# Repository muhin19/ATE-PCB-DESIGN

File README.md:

ATE PCB Design

📌 Project Overview
This project involves the design and development of a Printed Circuit Board (PCB) for an Automatic Test Equipment (ATE) application. It includes PCB layout design, component placement, track routing, and design verification to achieve a reliable and organized hardware layout.

🎯 Objectives
Design a PCB layout for an ATE application.
Arrange electronic components efficiently.
Route signal and power connections properly.
Maintain a clear and organized PCB layout.
Prepare PCB design files for manufacturing and further testing.

🛠️ Tools Used
PCB Design Software: KiCad
Schematic Design
Component Placement and Routing
Design Rule Check (DRC)

📂 Project Files
Schematic/ – Circuit schematic files.
PCB_Layout/ – PCB layout and board design files.
Gerber/ – Manufacturing output files, if available.
BOM/ – Bill of Materials, if available.
Images/ – PCB layout screenshots and 3D views.

⚙️ Design Features
Organized component placement.
PCB trace routing and connectivity.
Power and signal routing considerations.
Design verification using applicable PCB design rules.
Manufacturing file generation, if completed.

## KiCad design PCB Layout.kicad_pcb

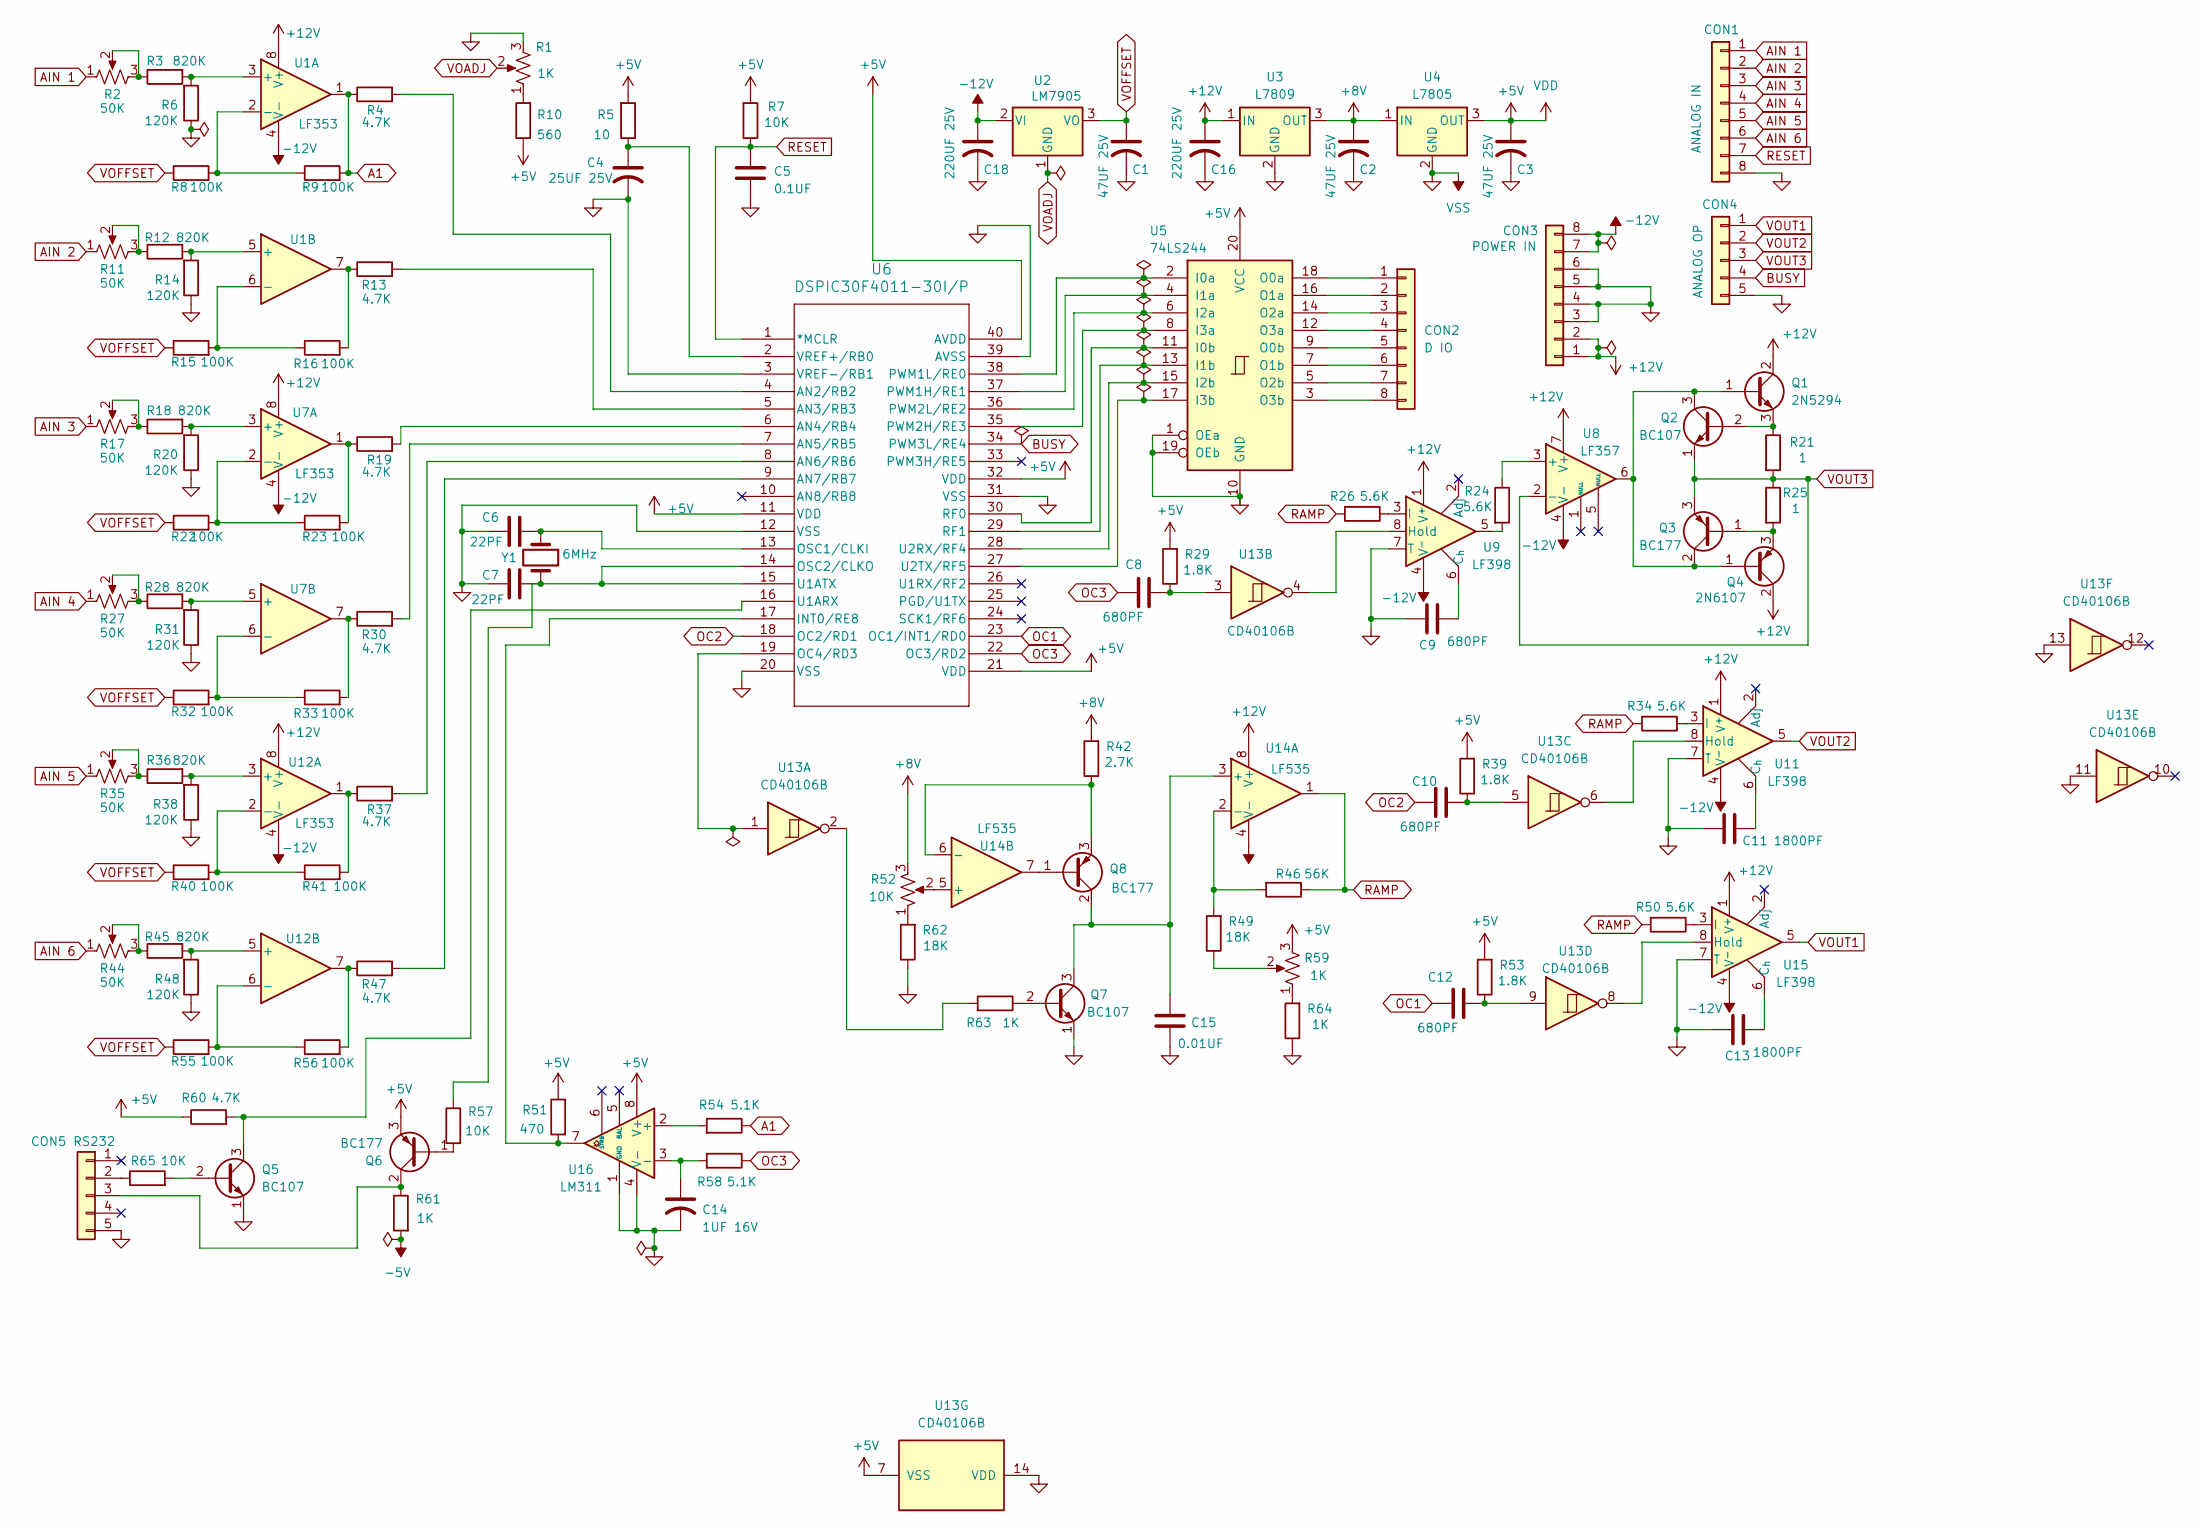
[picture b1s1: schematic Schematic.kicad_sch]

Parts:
C1, C2, C3: 47UF 25V; C_Radial_D5.0mm_H11.0mm_P2.00mm
C4: 25UF 25V; C_Radial_D5.0mm_H11.0mm_P2.00mm
C5: 0.1UF; C_Radial_D5.0mm_H11.0mm_P2.00mm
C6, C7: 22PF; C_Disc_D5.1mm_W3.2mm_P5.00mm
C8, C9, C10, C12: 680PF; C_Disc_D6.0mm_W4.4mm_P5.00mm
C11, C13: 1800PF; C_Disc_D6.0mm_W4.4mm_P5.00mm
C14: 1UF 16V; C_Radial_D5.0mm_H11.0mm_P2.00mm
C15: 0.01UF; C_Axial_L17.0mm_D6.5mm_P20.00mm_Horizontal
C16, C18: 220UF 25V; C_Radial_D8.0mm_H11.5mm_P3.50mm
CON1: ANALOG IN; JST_XH_B8B-XH-A_1x08_P2.50mm_Vertical
CON2: D IO; JST_XH_B8B-XH-A_1x08_P2.50mm_Vertical
CON3: POWER IN; JST_XH_B8B-XH-A_1x08_P2.50mm_Vertical
CON4: ANALOG OP; JST_XH_B5B-XH-A_1x05_P2.50mm_Vertical
CON5: RS232; JST_XH_B5B-XH-A_1x05_P2.50mm_Vertical
Q1: 2N5294; TO-220-3_Vertical
Q2, Q5, Q7: BC107; TO-18-3
Q3, Q6, Q8: BC177; TO-18-3
Q4: 2N6107; TO-220-3_Vertical
R1, R59: 1K; Potentiometer_Bourns_3296W_Vertical
R2, R11, R17, R27, R35, R44: 50K; Potentiometer_Bourns_3296W_Vertical
R3, R12, R18, R28, R36, R45: 820K; R_Axial_DIN0207_L6.3mm_D2.5mm_P10.16mm_Horizontal
R4, R13, R19, R30, R37, R47, R60: 4.7K; R_Axial_DIN0207_L6.3mm_D2.5mm_P10.16mm_Horizontal
R5: 10; R_Axial_DIN0207_L6.3mm_D2.5mm_P10.16mm_Horizontal
R6, R14, R20, R31, R38, R48: 120K; R_Axial_DIN0207_L6.3mm_D2.5mm_P10.16mm_Horizontal
R7, R57, R65: 10K; R_Axial_DIN0207_L6.3mm_D2.5mm_P10.16mm_Horizontal
R8, R9, R15, R16, R22, R23, R32, R33, R40, R41, R55, R56: 100K; R_Axial_DIN0207_L6.3mm_D2.5mm_P10.16mm_Horizontal
R10: 560; R_Axial_DIN0207_L6.3mm_D2.5mm_P10.16mm_Horizontal
R21, R25: 1; R_Axial_DIN0207_L6.3mm_D2.5mm_P10.16mm_Horizontal
R24, R26, R34, R50: 5.6K; R_Axial_DIN0207_L6.3mm_D2.5mm_P10.16mm_Horizontal
R29, R39, R53: 1.8K; R_Axial_DIN0207_L6.3mm_D2.5mm_P10.16mm_Horizontal
R42: 2.7K; R_Axial_DIN0207_L6.3mm_D2.5mm_P10.16mm_Horizontal
R46: 56K; R_Axial_DIN0207_L6.3mm_D2.5mm_P10.16mm_Horizontal
R49, R62: 18K; R_Axial_DIN0207_L6.3mm_D2.5mm_P10.16mm_Horizontal
R51: 470; R_Axial_DIN0207_L6.3mm_D2.5mm_P10.16mm_Horizontal
R52: 10K; Potentiometer_Bourns_3296W_Vertical
R54, R58: 5.1K; R_Axial_DIN0207_L6.3mm_D2.5mm_P10.16mm_Horizontal
R61, R63, R64: 1K; R_Axial_DIN0207_L6.3mm_D2.5mm_P10.16mm_Horizontal
U1, U7, U12: LF353; DIP-8_W7.62mm
U2: LM7905; TO-220-3_Vertical
U3: L7809; TO-220-3_Vertical
U4: L7805; TO-220-3_Vertical
U5: 74LS244; DIP-20_W7.62mm
U6: DSPIC30F4011-30I/P; DIP-40_W15.24mm
U8: LF357; DIP-8_W7.62mm
U9, U11, U15: LF398; DIP-8_W7.62mm
U13: CD40106B; DIP-14_W7.62mm
U14: LF535; DIP-8_W7.62mm
U16: LM311; DIP-8_W7.62mm
Y1: 6MHz; Crystal_HC49-U_Vertical

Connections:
+5V: C3.1, Q6.3 (E), R5.2, R7.2, R10.1, R29.2, R39.2, R51.1, R53.2, R59.3, R60.1, U4.3 (OUT), U5.20 (VCC), U6.11 (VDD), U6.21 (VDD), U6.32 (VDD), U6.40 (AVDD), U13.7 (VSS), U16.8 (V+)
+8V: C2.1, R42.2, R52.3, U3.3 (OUT), U4.1 (IN)
+12V: C16.1, CON3.1, CON3.2, Q1.2 (C), Q4.2 (C), U1.8 (V+), U3.1 (IN), U7.8 (V+), U8.7 (V+), U9.1 (V^{+}), U11.1 (V^{+}), U12.8 (V+), U14.8 (V+), U15.1 (V^{+})
-5V: R61.2
-12V: C18.1, CON3.7, CON3.8, U1.4 (V-), U2.2 (VI), U7.4 (V-), U8.4 (V-), U9.4 (V^{-}), U11.4 (V^{-}), U12.4 (V-), U14.4 (V-), U15.4 (V^{-})
<NO NET>: C14.2, C15.2, Q7.1 (E), R62.1, R64.1, U13.14 (VDD), U16.1 (GND), U16.4 (V-)
A1: R4.1, R9.2, R54.1, U1.1
AIN 1: CON1.1, R2.1
AIN 2: CON1.2, R11.1
AIN 3: CON1.3, R17.1
AIN 4: CON1.4, R27.1
AIN 5: CON1.5, R35.1
AIN 6: CON1.6, R44.1
BUSY: CON4.4, U6.34 (PWM3L/RE4)
GND: C1.2, C2.2, C3.2, C4.2, C5.2, C6.1, C7.1, C9.1, C11.1, C13.1, C16.2, C18.2, CON1.8, CON3.3, CON3.4, CON3.5, CON3.6, CON4.5, CON5.5, Q5.1 (E), R1.3, R6.1, R14.1, R20.1, R31.1, R38.1, R48.1, U3.2 (GND), U4.2 (GND), U5.1 (OEa), U5.10 (GND), U5.19 (OEb), U6.3 (VREF-/RB1), U6.12 (VSS), U6.20 (VSS), U6.31 (VSS), U6.39 (AVSS), U9.7 (T), U11.7 (T), U13.11, U13.13, U15.7 (T)
unnamed: C8.2, R29.1, U13.3
unnamed: C10.2, R39.1, U13.5
unnamed: C12.2, R53.1, U13.9
unnamed: CON2.1, U5.18 (O0a)
unnamed: CON2.2, U5.16 (O1a)
unnamed: CON2.3, U5.14 (O2a)
unnamed: CON2.4, U5.12 (O3a)
unnamed: CON2.5, U5.9 (O0b)
unnamed: CON2.6, U5.7 (O1b)
unnamed: CON2.7, U5.5 (O2b)
unnamed: CON2.8, U5.3 (O3b)
unnamed: CON5.2, R65.1
unnamed: CON5.3, Q6.2 (C), R61.1
unnamed: Q1.1 (B), Q2.3 (C), Q3.2 (C), Q4.1 (B), U8.6
unnamed: Q1.3 (E), Q2.2 (B), R21.1
unnamed: Q3.1 (B), Q4.3 (E), R25.2
unnamed: Q5.2 (B), R65.2
unnamed: Q5.3 (C), R60.2, U6.16 (U1ARX)
unnamed: Q6.1 (B), R57.2
unnamed: Q7.2 (B), R63.1
unnamed: C15.1, Q7.3 (C), Q8.2 (C), U14.3 (+)
unnamed: Q8.1 (B), U14.7
unnamed: Q8.3 (E), R42.1, U14.6 (-)
unnamed: R1.1, R10.2
unnamed: R2.2, R2.3, R3.1
unnamed: R11.2, R11.3, R12.1
unnamed: R13.1, R16.2, U1.7
unnamed: R17.2, R17.3, R18.1
unnamed: R19.1, R23.2, U7.1
unnamed: R24.2, U9.5
unnamed: R27.2, R27.3, R28.1
unnamed: R30.1, R33.2, U7.7
unnamed: R35.2, R35.3, R36.1
unnamed: R37.1, R41.2, U12.1
unnamed: R44.2, R44.3, R45.1
unnamed: R47.1, R56.2, U12.7
unnamed: R49.1, R59.2
unnamed: R52.1, R62.2
unnamed: R59.1, R64.2
unnamed: R63.2, U13.2
unnamed: R3.2, R6.2, U1.3 (+)
unnamed: R8.2, R9.1, U1.2 (-)
unnamed: R12.2, R14.2, U1.5 (+)
unnamed: R15.2, R16.1, U1.6 (-)
unnamed: U5.2 (I0a), U6.38 (PWM1L/RE0)
unnamed: U5.11 (I0b), U6.30 (RF0)
unnamed: U5.4 (I1a), U6.37 (PWM1H/RE1)
unnamed: U5.13 (I1b), U6.29 (RF1)
unnamed: U5.6 (I2a), U6.36 (PWM2L/RE2)
unnamed: U5.15 (I2b), U6.28 (U2RX/RF4)
unnamed: U5.8 (I3a), U6.35 (PWM2H/RE3)
unnamed: U5.17 (I3b), U6.27 (U2TX/RF5)
unnamed: R4.2, U6.4 (AN2/RB2)
unnamed: R13.2, U6.5 (AN3/RB3)
unnamed: R19.2, U6.6 (AN4/RB4)
unnamed: R30.2, U6.7 (AN5/RB5)
unnamed: R37.2, U6.8 (AN6/RB6)
unnamed: R47.2, U6.9 (AN7/RB7)
unnamed: R51.2, U6.17 (INT0/RE8), U16.7
unnamed: U6.19 (OC4/RD3), U13.1
unnamed: C6.2, U6.13 (OSC1/CLKI), Y1.1
unnamed: C7.2, R57.1, U6.14 (OSC2/CLKO), U6.15 (U1ATX), Y1.2
unnamed: C4.1, R5.1, U6.2 (VREF+/RB0)
unnamed: R18.2, R20.2, U7.3 (+)
unnamed: R22.2, R23.1, U7.2 (-)
unnamed: R28.2, R31.2, U7.5 (+)
unnamed: R32.2, R33.1, U7.6 (-)
unnamed: R24.1, U8.3 (+)
unnamed: C9.2, U9.6 (C_{h})
unnamed: U9.8 (Hold), U13.4
unnamed: R26.1, U9.3 (I)
unnamed: C11.2, U11.6 (C_{h})
unnamed: U11.8 (Hold), U13.6
unnamed: R34.1, U11.3 (I)
unnamed: R36.2, R38.2, U12.3 (+)
unnamed: R40.2, R41.1, U12.2 (-)
unnamed: R45.2, R48.2, U12.5 (+)
unnamed: R55.2, R56.1, U12.6 (-)
unnamed: R46.2, R49.2, U14.2 (-)
unnamed: R52.2, U14.5 (+)
unnamed: C13.2, U15.6 (C_{h})
unnamed: U13.8, U15.8 (Hold)
unnamed: R50.1, U15.3 (I)
unnamed: R54.2, U16.2 (+)
unnamed: C14.1, R58.2, U16.3 (-)
OC1: C12.1, U6.23 (OC1/INT1/RD0)
OC2: C10.1, U6.18 (OC2/RD1)
OC3: C8.1, R58.1, U6.22 (OC3/RD2)
RAMP: R26.2, R34.2, R46.1, R50.2, U14.1
RESET: C5.1, CON1.7, R7.1, U6.1 (*MCLR)
VOADJ: R1.2, U2.1 (GND)
VOFFSET: C1.1, R8.1, R15.1, R22.1, R32.1, R40.1, R55.1, U2.3 (VO)
VOUT1: CON4.1, U15.5
VOUT2: CON4.2, U11.5
VOUT3: CON4.3, Q2.1 (E), Q3.3 (E), R21.2, R25.1, U8.2 (-)

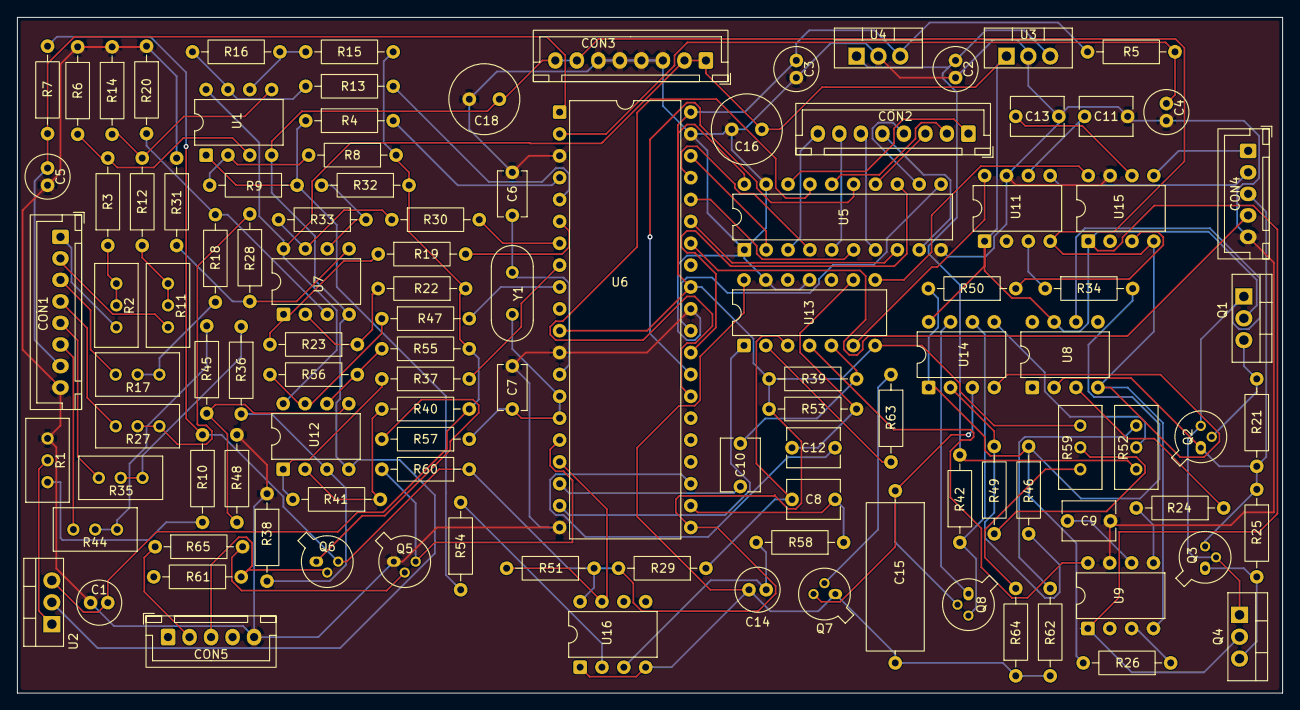
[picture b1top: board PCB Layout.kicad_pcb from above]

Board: 2 copper layers, 147.0 x 78.5 mm, 110 parts (0 on the bottom side), 109 nets.

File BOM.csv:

"Reference","Qty","Value","DNP","Exclude from BOM","Exclude from Board","Footprint","Datasheet"
"C1,C2,C3","3","47UF 25V","","","","Capacitor_THT:C_Radial_D5.0mm_H11.0mm_P2.00mm",""
"C4","1","25UF 25V","","","","Capacitor_THT:C_Radial_D5.0mm_H11.0mm_P2.00mm",""
"C5","1","0.1UF","","","","Capacitor_THT:C_Radial_D5.0mm_H11.0mm_P2.00mm",""
"C6,C7","2","22PF","","","","Capacitor_THT:C_Disc_D5.1mm_W3.2mm_P5.00mm",""
"C8,C9,C10,C12","4","680PF","","","","Capacitor_THT:C_Disc_D6.0mm_W4.4mm_P5.00mm",""
"C11,C13","2","1800PF","","","","Capacitor_THT:C_Disc_D6.0mm_W4.4mm_P5.00mm",""
"C14","1","1UF 16V","","","","Capacitor_THT:C_Radial_D5.0mm_H11.0mm_P2.00mm",""
"C15","1","0.01UF","","","","Capacitor_THT:C_Axial_L17.0mm_D6.5mm_P20.00mm_Horizontal",""
"C16,C18","2","220UF 25V","","","","Capacitor_THT:C_Radial_D8.0mm_H11.5mm_P3.50mm",""
"CON1","1","ANALOG IN","","","","Connector_JST:JST_XH_B8B-XH-A_1x08_P2.50mm_Vertical",""
"CON2","1","D IO","","","","Connector_JST:JST_XH_B8B-XH-A_1x08_P2.50mm_Vertical",""
"CON3","1","POWER IN","","","","Connector_JST:JST_XH_B8B-XH-A_1x08_P2.50mm_Vertical",""
"CON4","1","ANALOG OP","","","","Connector_JST:JST_XH_B5B-XH-A_1x05_P2.50mm_Vertical",""
"CON5","1","RS232","","","","Connector_JST:JST_XH_B5B-XH-A_1x05_P2.50mm_Vertical",""
"Q1","1","2N5294","","","","Package_TO_SOT_THT:TO-220-3_Vertical",""
"Q2,Q5,Q7","3","BC107","","","","Package_TO_SOT_THT:TO-18-3","http://www.b-kainka.de/Daten/Transistor/BC108.pdf"
"Q3,Q6,Q8","3","BC177","","","","Package_TO_SOT_THT:TO-18-3",""
"Q4","1","2N6107","","","","Package_TO_SOT_THT:TO-220-3_Vertical",""
"R1,R59","2","1K","","","","Potentiometer_THT:Potentiometer_Bourns_3296W_Vertical",""
"R2,R11,R17,R27,R35,R44","6","50K","","","","Potentiometer_THT:Potentiometer_Bourns_3296W_Vertical",""
"R3,R12,R18,R28,R36,R45","6","820K","","","","Resistor_THT:R_Axial_DIN0207_L6.3mm_D2.5mm_P10.16mm_Horizontal",""
"R4,R13,R19,R30,R37,R47,R60","7","4.7K","","","","Resistor_THT:R_Axial_DIN0207_L6.3mm_D2.5mm_P10.16mm_Horizontal",""
"R5","1","10","","","","Resistor_THT:R_Axial_DIN0207_L6.3mm_D2.5mm_P10.16mm_Horizontal",""
"R6,R14,R20,R31,R38,R48","6","120K","","","","Resistor_THT:R_Axial_DIN0207_L6.3mm_D2.5mm_P10.16mm_Horizontal",""
"R7,R57,R65","3","10K","","","","Resistor_THT:R_Axial_DIN0207_L6.3mm_D2.5mm_P10.16mm_Horizontal",""
"R8,R9,R15,R16,R22,R23,R32,R33,R40,R41,R55,R56","12","100K","","","","Resistor_THT:R_Axial_DIN0207_L6.3mm_D2.5mm_P10.16mm_Horizontal",""
"R10","1","560","","","","Resistor_THT:R_Axial_DIN0207_L6.3mm_D2.5mm_P10.16mm_Horizontal",""
"R21,R25","2","1","","","","Resistor_THT:R_Axial_DIN0207_L6.3mm_D2.5mm_P10.16mm_Horizontal",""
"R24,R26,R34,R50","4","5.6K","","","","Resistor_THT:R_Axial_DIN0207_L6.3mm_D2.5mm_P10.16mm_Horizontal",""
"R29,R39,R53","3","1.8K","","","","Resistor_THT:R_Axial_DIN0207_L6.3mm_D2.5mm_P10.16mm_Horizontal",""
"R42","1","2.7K","","","","Resistor_THT:R_Axial_DIN0207_L6.3mm_D2.5mm_P10.16mm_Horizontal",""
"R46","1","56K","","","","Resistor_THT:R_Axial_DIN0207_L6.3mm_D2.5mm_P10.16mm_Horizontal",""
"R49,R62","2","18K","","","","Resistor_THT:R_Axial_DIN0207_L6.3mm_D2.5mm_P10.16mm_Horizontal",""
"R51","1","470","","","","Resistor_THT:R_Axial_DIN0207_L6.3mm_D2.5mm_P10.16mm_Horizontal",""
"R52","1","10K","","","","Potentiometer_THT:Potentiometer_Bourns_3296W_Vertical",""
"R54,R58","2","5.1K","","","","Resistor_THT:R_Axial_DIN0207_L6.3mm_D2.5mm_P10.16mm_Horizontal",""
"R61,R63,R64","3","1K","","","","Resistor_THT:R_Axial_DIN0207_L6.3mm_D2.5mm_P10.16mm_Horizontal",""
"U1,U7,U12","3","LF353","","","","Package_DIP:DIP-8_W7.62mm","http://www.ti.com/lit/ds/symlink/tl071.pdf"
"U2","1","LM7905","","","","Package_TO_SOT_THT:TO-220-3_Vertical","https://www.onsemi.com/pub/Collateral/MC7900-D.PDF"
"U3","1","L7809","","","","Package_TO_SOT_THT:TO-220-3_Vertical","http://www.st.com/content/ccc/resource/technical/document/da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"
"U4","1","L7805","","","","Package_TO_SOT_THT:TO-220-3_Vertical","http://www.st.com/content/ccc/resource/technical/document/da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"
"U5","1","74LS244","","","","Package_DIP:DIP-20_W7.62mm","http://www.ti.com/lit/ds/symlink/sn74ls244.pdf"
"U6","1","DSPIC30F4011-30I/P","","","","Package_DIP:DIP-40_W15.24mm","DSPIC30F4011-30I/P"
"U8","1","LF357","","","","Package_DIP:DIP-8_W7.62mm","http://www.ti.com/lit/ds/symlink/lf357.pdf"
"U9,U11,U15","3","LF398","","","","Package_DIP:DIP-8_W7.62mm","http://www.ti.com/lit/ds/symlink/lf398-n.pdf"
"U13","1","CD40106B","","","","Package_DIP:DIP-14_W7.62mm","https://assets.nexperia.com/documents/data-sheet/HEF40106B.pdf"
"U14","1","LF535","","","","Package_DIP:DIP-8_W7.62mm","http://www.ti.com/lit/ds/symlink/tl071.pdf"
"U16","1","LM311","","","","Package_DIP:DIP-8_W7.62mm","https://www.st.com/resource/en/datasheet/lm311.pdf"
"Y1","1","6MHz","","","","Crystal:Crystal_HC49-U_Vertical",""
